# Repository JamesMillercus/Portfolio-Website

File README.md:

# Portfolio-Website
A repository containing the code for my portfolio website.

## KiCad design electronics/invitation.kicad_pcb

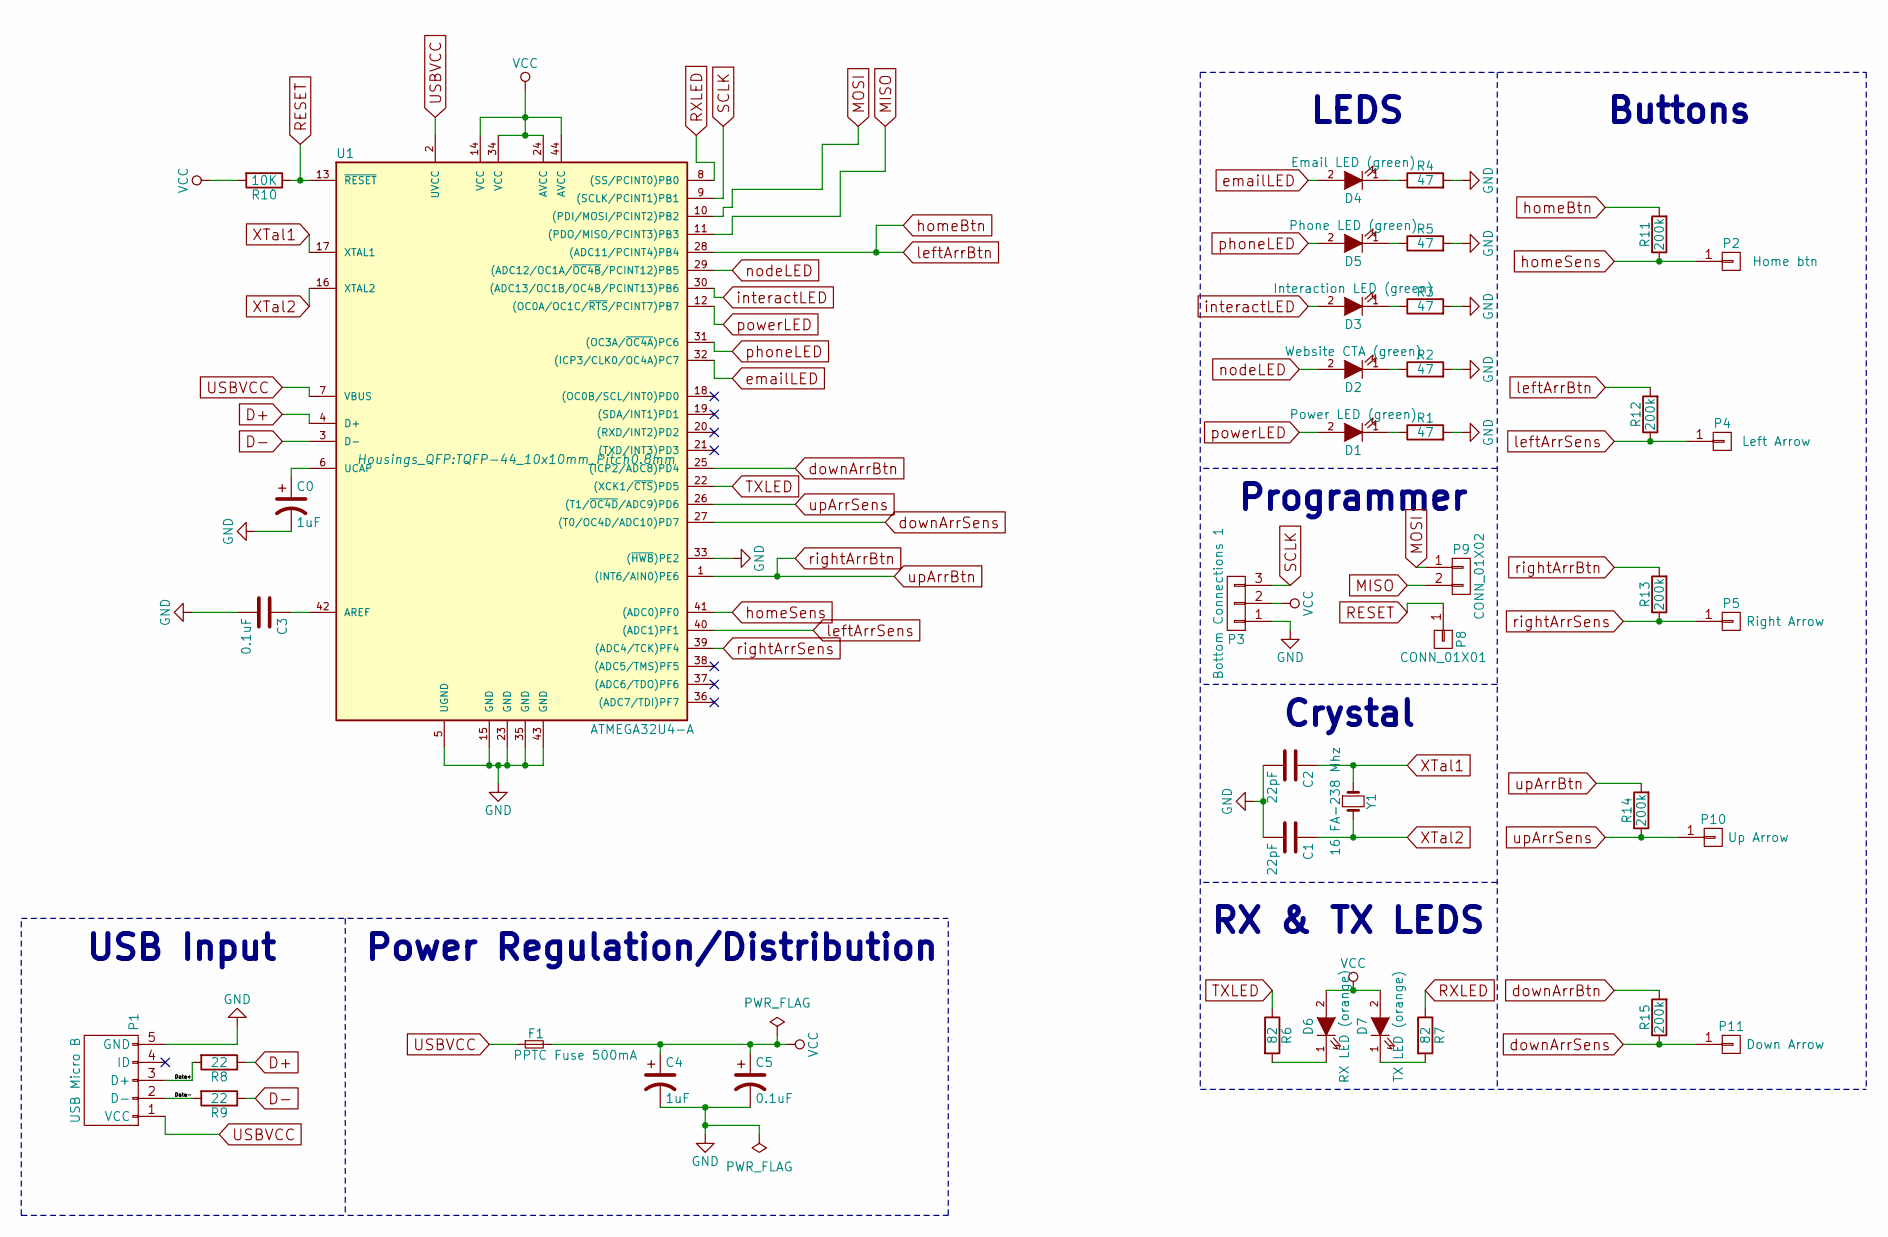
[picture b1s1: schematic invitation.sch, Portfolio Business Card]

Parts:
C0, C4: 1uF; CP_Tantalum_Case-R_EIA-2012-12_Reflow
C1, C2: 22pF; C_0805
C3: 0.1uF; C_0805
C5: 0.1uF; CP_Tantalum_Case-R_EIA-2012-12_Reflow
D1: Power LED (green); LED_0805
D2: Website CTA (green); LED_0805
D3: Interaction LED (green); LED_0805
D4: Email LED (green); LED_0805
D5: Phone LED (green); LED_0805
D6: RX LED (orange); LED_0805
D7: TX LED (orange); LED_0805
F1: PPTC Fuse 500mA; Fuse_SMD1206_Reflow
P1: USB Micro B; FCI_10103594-0001LF
P2: Home btn; JMLogoFinalSS
P3: Bottom Connections 1; SL-103-X-XX_1x03
P4: Left Arrow; leftArrowSS
P5: Right Arrow; rightArrowSS
P8: CONN_01X01; SL-101-X-XX_1x01
P9: CONN_01X02; SL-102-X-XX_1x02
P10: Up Arrow; upArrowSS
P11: Down Arrow; downArrowSS
R1, R2, R3, R4, R5: 47; R_0805
R6, R7: 82; R_0805
R8, R9: 22; R_0805
R10: 10K; R_0805
R11, R12, R13, R14, R15: 200k; R_0805_2012Metric
U1: ATMEGA32U4-A; TQFP-44_10x10mm_Pitch0.8mm
Y1: 16 FA-238 Mhz; crystal_FA238-TSX3225

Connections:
/Data+: P1.3 (D+), R8.2
/Data-: P1.2 (D-), R9.2
D+: R8.1, U1.4 (D+)
D-: R9.1, U1.3 (D-)
GND: C0.2, C1.2, C2.2, C3.2, C4.2, C5.2, P1.5 (GND), P3.1, R1.2, R2.2, R3.2, R4.2, R5.2, U1.5 (UGND), U1.15 (GND), U1.23 (GND), U1.33 ((~HWB~)PE2), U1.35 (GND), U1.43 (GND)
MISO: P9.2, U1.11 ((PDO/MISO/PCINT3)PB3)
MOSI: P9.1, U1.10 ((PDI/MOSI/PCINT2)PB2)
unnamed: C0.1, U1.6 (UCAP)
unnamed: C3.1, U1.42 (AREF)
unnamed: D1.1 (K), R1.1
unnamed: D2.1 (K), R2.1
unnamed: D3.1 (K), R3.1
unnamed: D4.1 (K), R4.1
unnamed: D5.1 (K), R5.1
unnamed: D6.1 (K), R6.2
unnamed: D7.1 (K), R7.2
RESET: P8.1, R10.1, U1.13 (~RESET~)
RXLED: R7.1, U1.8 ((SS/PCINT0)PB0)
SCLK: P3.3, U1.9 ((SCLK/PCINT1)PB1)
TXLED: R6.1, U1.22 ((XCK1/~CTS~)PD5)
USBVCC: F1.1, P1.1 (VCC), U1.2 (UVCC), U1.7 (VBUS)
VCC: C4.1, C5.1, D6.2 (A), D7.2 (A), F1.2, P3.2, R10.2, U1.14 (VCC), U1.24 (AVCC), U1.34 (VCC), U1.44 (AVCC)
XTal1: C2.1, U1.17 (XTAL1), Y1.1
XTal2: C1.1, U1.16 (XTAL2), Y1.2
downArrBtn: R15.2, U1.25 ((ICP2/ADC8)PD4)
downArrSens: P11.1, R15.1, U1.27 ((T0/OC4D/ADC10)PD7)
emailLED: D4.2 (A), U1.32 ((ICP3/CLK0/OC4A)PC7)
homeBtn: R11.2, R12.2, U1.28 ((ADC11/PCINT4)PB4)
homeSens: P2.1, R11.1, U1.41 ((ADC0)PF0)
interactLED: D3.2 (A), U1.30 ((ADC13/OC1B/OC4B/PCINT13)PB6)
leftArrSens: P4.1, R12.1, U1.40 ((ADC1)PF1)
nodeLED: D2.2 (A), U1.29 ((ADC12/OC1A/~OC4B~/PCINT12)PB5)
phoneLED: D5.2 (A), U1.31 ((OC3A/~OC4A~)PC6)
powerLED: D1.2 (A), U1.12 ((OC0A/OC1C/~RTS~/PCINT7)PB7)
rightArrBtn: R13.2, R14.2, U1.1 ((INT6/AIN0)PE6)
rightArrSens: P5.1, R13.1, U1.39 ((ADC4/TCK)PF4)
upArrSens: P10.1, R14.1, U1.26 ((T1/~OC4D~/ADC9)PD6)

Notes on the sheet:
USB Input
Power Regulation/Distribution
LEDS
Buttons
Programmer
RX & TX LEDS
Crystal

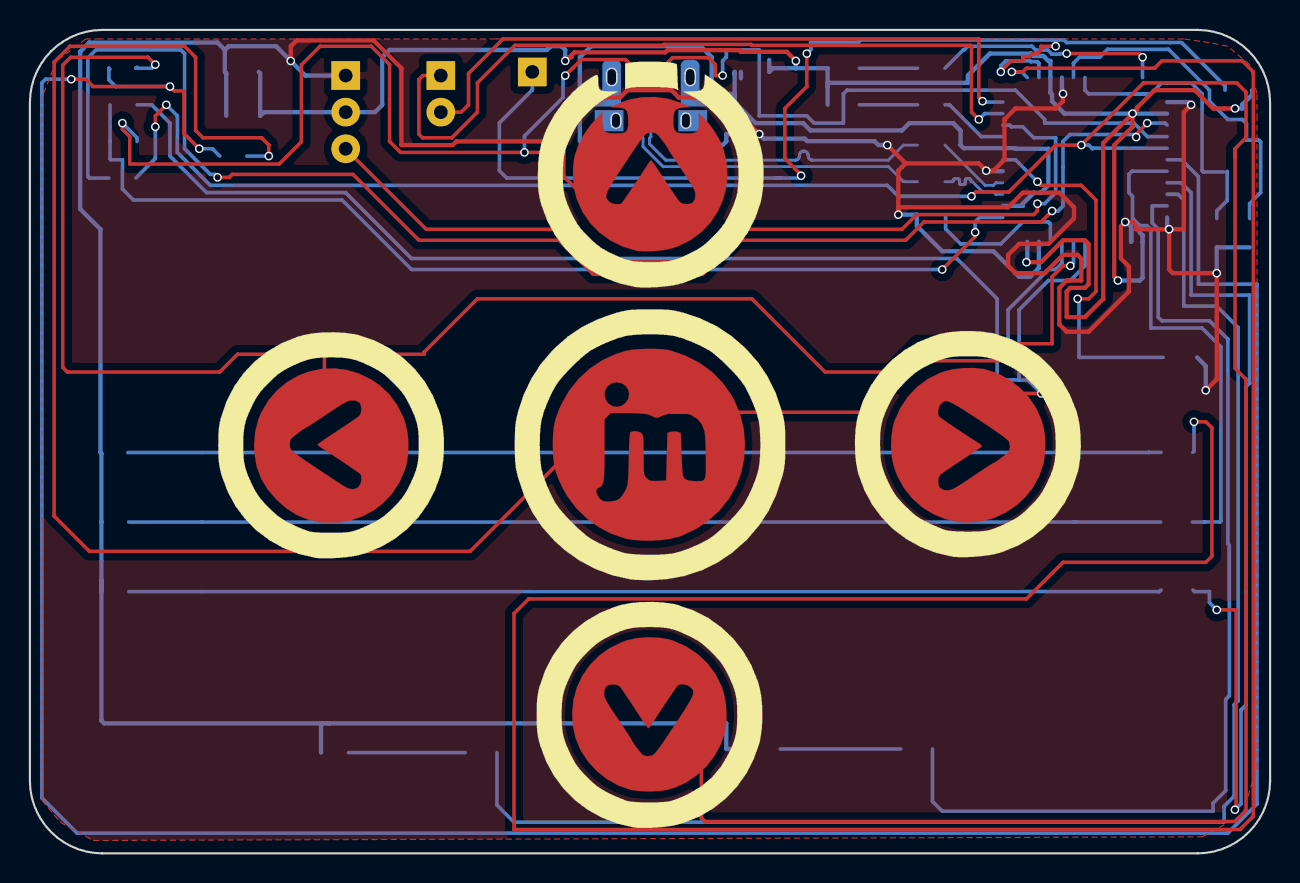
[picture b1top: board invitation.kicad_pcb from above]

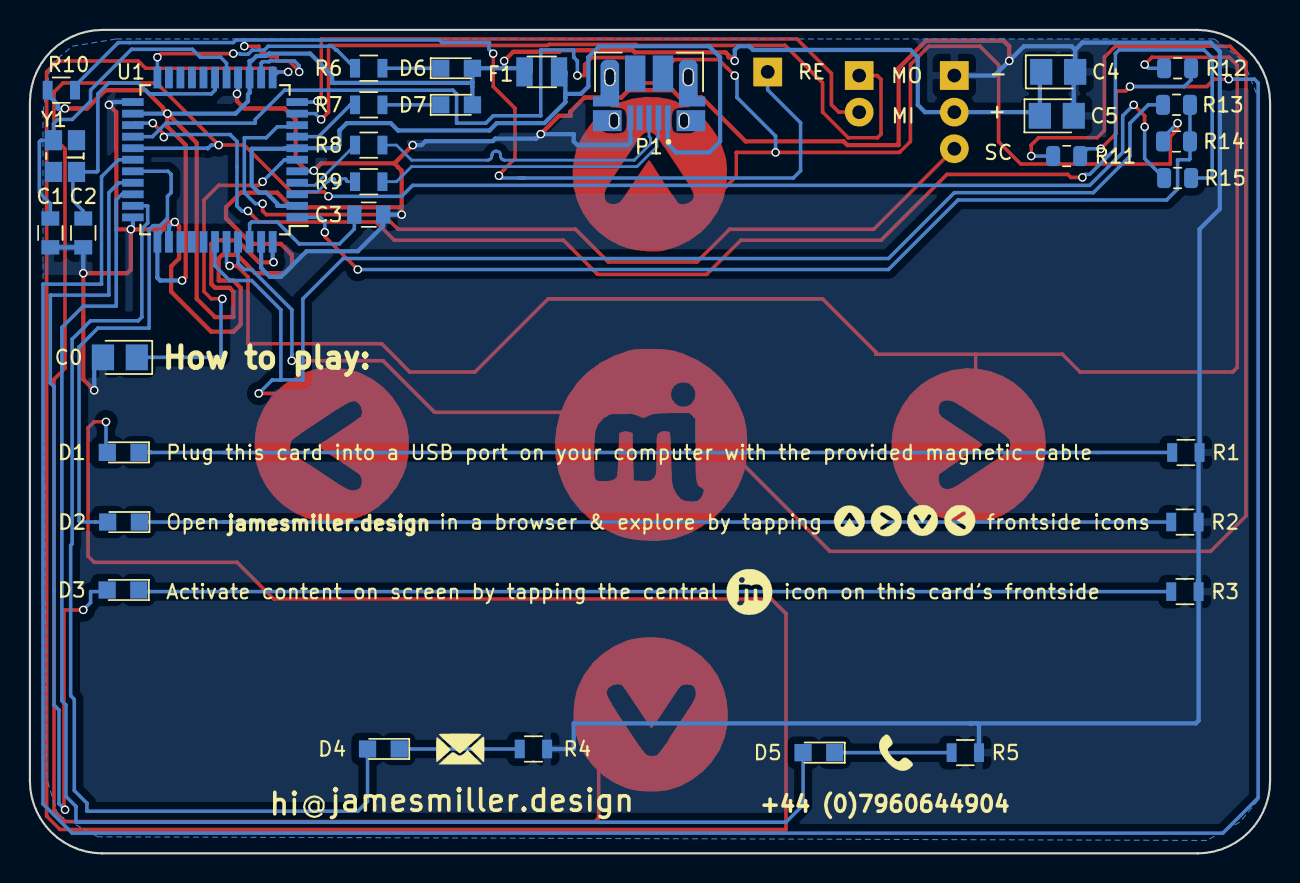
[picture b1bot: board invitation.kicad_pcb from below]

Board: 2 copper layers, 86.1 x 57.2 mm, 40 parts (32 on the bottom side), 37 nets.

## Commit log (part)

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2016-10-17 First commit: Uploading files to git for the first time.
2016-10-19 Commit 5: notes to myself about how to load videos
2016-10-24 Commit 7.1 - Updated Distribution folder with changes made in commit 7
2016-10-30 Commit 10:
    - When scrolled over, made videos auto play + reveal once they are loaded
2016-11-08 Commit 14:
    - Implemented full screen functionality
    - Still needs to be muted/unmuted + requires css changes on the video
2016-11-24 Commit 17 (whilst in LA): Added iPad + iPhone full screen video playing functionality
2016-12-02 Commit 21 (last commit before return to the UK): Fixed bugs with video opener and electronic invitation buttons, also implemented some design changes and prepared design assets for the plane journey
2016-12-06 Commit 25: Updated list of bugs to fix
2016-12-22 Commit 29: Fix scrolling bugs when initially loading the website and dragging mouse into browser, finalised central text functionality, added beer pump project.
2016-12-30 Commit 33: Updated hero changing function so that it only triggers if an Arduino is present, all logic is dealt with in the back end if hero does need to change (also means that if CMS is introduced,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
2017-01-16 Commit 38: Business card pre-production
2017-01-25 Commit 41: Updated Business Card BOM + PCB + Schematic to make sure components can be sourced.
2017-01-30 Commit 45: Continuing to optimise code by reprogramming global variables as objects.
2017-02-06 Commt 49: uncompleted changes
2017-02-18 Commit 53: Constructor function is now fully implemented
2017-09-11 Continue development on this branch.
2017-10-01 remove ignore
2017-10-02 SSL attempt
2017-10-28 PCB ready to print
2018-05-29 Implemented basic front end layout
2018-06-14 Scrolling animation positions and page sizing updated in preparation for item text content to be inserted
2018-07-02 Implemented device detection, browser detection needs state syncing
2018-07-06 Tidied Device and Browser detection HOCs
2018-07-08 Serving html content to screen, requires styling
2018-07-13 Prepared code ready for device specific functionality & styling
2018-07-17 Tidied Item component into ItemContainer and ItemText.
    To do:
    - Turn each component into a Tablet version, starting with GridContainer
2018-07-20 Implemented basic tablet functionality and made styling for device types even simpler by referencing .grid-container-${device} in scss
2018-07-22 Mail icon doesn’t open new tab
2018-07-26 Updated Merck and SAP golf gifs.
    Next step:
    - print out designs from pinterest into sketchbook
    - plan how the final designs will look
2018-08-04 Adjusting items to fit the new screen size
    Next steps:
    1. finish re-adjusting items to fit new screen size & make text look neater
    2. set heroLogo to expand to james miller on scroll over
    3. when scrolled out return to logo
    4. set hero text to normal font when icon scroll occurs
    5. set james miller to animate when scrolled over
2018-08-06 Prepared HeroText component for animation by tidying into parent and children
    Next steps:
    1. finalise design for logo and hero text
    2. hero text animation on change
    3. opening site animation
    4. implement for tablet & mobile
    5. design and implement error pages
2018-08-13 Finished implementing mouse scroll
    Next steps:
    1. hero text animation on change
    2. finalise colours for logo and hero text
    3. opening site animation
    4. implement for tablet & mobile
    5. design and implement error pages
2018-08-19 Continued to further reformat the hero text animation, steps to completion in code
    Next steps:
    1. hero text animation on change
    2. finalise colours for logo and hero text
    3. opening site animation
    4. Finalise hero area (text content, font, vertical / horizontal size of area)
    5. Animate hero to grow when scrolled over, items shrink
2018-08-26 hero nav updates almost complete
    Next steps:
    1. finalise colours for logo and hero text
    2. Finalise hero area (text content, font, vertical / horizontal size of area)
    3. Animate hero to grow when scrolled over, items shrink
    4. opening site animation
    Post alpha:
2018-08-30 Animated items
    Final alpha step:
    1. animate logo
    Beta:
    1. Design and implement error pages
    2. Final implementation for tablet & mobile
    3. Browser testing
2018-09-07 Mobile version complete
    Beta:
    1. Final implementation for tablet
    2. Browser testing
    3. Launch
    4. CodeSplitting
    5. Populate all social platforms with content
2018-09-12 Only enabled mouse movement on Chrome browser.
    To do: Windows 10: Fix hero area grid, Linux: test on camerons’s computer
    Beta:
    1. Final browser & device testing (launch)
    2. Prepare pages to be reusable (portfolio + tech pages)
    3. CodeSplitting
    4. Populate all social platforms with content
2018-09-16 SSL update
2018-09-21 Pages are prepared for reuse, tech page now created, animations implemented
    Beta:
    1. CodeSplitting (also get urls working in react)
    2. Populate all website + social platforms with content
    3. GDPR / Icons purchase (noun project) / copy right
2018-09-26 To do: Update heroIcons sizes for tech page, ready to put content in!!
    Beta:
    1. Populate all website + social platforms with content
    2. GDPR / Icons purchase (noun project) / copy right
    3. Jenkins (CI / CD)
2018-09-29 Updated GitHub and following links: apps, cms, architecture and blockchain links.
    Beta final to do:
    1. Content on other platforms (GitHub / LinkedIn / Behance / Hackster)
    2. Update visualise, prototype and IOT links
    3. Icons purchase (noun project) / copy right
2018-09-30 Beat Launched with CI!!!!!!!
2018-09-30 final push
2018-10-01 remove test
2018-10-01 push analytics
2018-10-04 push linkedin profile
2018-10-07 Update .rancher-pipeline.yml file
2018-10-07 test 3
2018-10-07 test 7
2018-10-07 launch site
2018-10-15 Hero Area styled
    - Implement config file for hero area
    - Implement redux
    - Break down Hero Area into multiple nested components
    - item component
    - video component
    - rework website for react360
2018-10-18 set variables from config via home page, tidy file structure (putting components into folders)
    to do:
    - ideally render content without renderToSurface
    - Either remove redux and routing, implement fake redux and all logic goes in client.js (not ideal)
    - implement functionality to render 3d objects within components
    - create services page
    - item component
2018-10-22 integrated scroll and click redux into the item component
    to do:
    - finish item component
    - video component
    - animation
    - create services page
    - integrate into reactjs app
2018-10-24 Working on video component, implemented native modules to resize 360 surfaces (woohoo)
    to do:
    - implement global redux-like store
    - video component
    - animation
    - create services page
    - integrate into reactjs app
2018-10-29 - completed video component playback
    to do:
    - redo app architecture to allow creation of all 8 items
    - test on mobile, tablet, oculus and vive
    - implement no script (error page)
    - implement error page for faulty/no accelerometer
2018-11-06 Implemented no script (error page)
    to do:
    - implement webvr button for mobile
    - implement error page for faulty/no accelerometer
    - test on mobile, tablet, oculus and vive
2018-11-09 Updated Webvr video component
2018-11-19 updated copy
2018-11-26 Implementing keyboard functionality, next step is to complete menu scrolling.
2018-12-12 Implementing keyboard functionality
    To do:
    - Complete electronic invite keyboard functionality (open hero feature)
    - Implement webvr-polyfill for mobile
    - More intuitive UX for webvr laptop experience
    - Fix getOSVersion.js HOC (in Lincoln)
    - Auto go-to webvr page on mobile if on iOS or android version .4 or higher
2018-12-19 Implemented functionality to switch between react360 / react versions of site based on device os.
    - Implement 2 versions of react360
    1. Webvr-polyfill for mobile (using Compositor.js), design & dev for gaze functionality
    2. Webvr laptop & mobile experience (Appropriate UX / UI for both)
    - Fix getOSVersion.js HOC (in Lincoln)
2019-01-02 Implemented gaze functionality for Hero, next stop is the Items (create circle hitbox around itemImage)
    - Complete react360
    1. Implement gaze functionality for polyfill version + design instruction page (implement in normal react).
    2. Instruction page for laptop + mobile version (implement in normal react).
    3. Enable click functionality for mobile non-webvr (without pointer)
    4. Fix video bugs and allow webvr version to play video without youtube (like laptop version)
    - Fix getOSVersion.js HOC (in Lincoln)
2019-01-10 Fixed bug for exiting videos on mobile + mobile webvr
    - Complete in react
    1. Design instruction page for mobile webvr + mobile + laptop
    2. Fix getOSVersion.js HOC (in Lincoln)
    - Rethink UX for site that gets you to pages
2019-01-21 Finished layout for instruction page.
    - Complete in react
    1. Detect if using VR headset
    - display different instructions for webvr
    - don’t allow split screen
    - don’t display non-webvr web page
    2. Create content for instruction page on headset webvr + mobile webvr + mobile + laptop
2019-02-17 Updated electronics for Chinese suppliers (V10) and allowed device type detection for react360 device based experiences.
    - To complete
    1. Display appropriate VR content based on device
    - vertical mobile display message to turn phone horizontally
    - iOS chrome iframe not playing when clicked!
    - VR instructions and video not working
    2. Create content for instruction page on headset webvr + mobile webvr + mobile + laptop
2019-05-13 Mobile (normal and WebVR) content and mobile interaction complete
    - To do
    1. Create content for
    a) instruction page
    laptop ( webvr / nonwebvr)
    b) updated projects (Egypt based on app content)
2019-05-22 Updated egypt css
    - To do
    a) update PCB (resize email icon to be bigger) and then purchase after latest test
    b) create final prototype box with a test letter
    c) order and assemble multiples
2019-06-13 Updated exit button on mobile
    - To do
    a) update PCB (resize email icon to be bigger) and then purchase after latest test
    b) order and assemble multiples
    c) update website’s small bugs & UX issues
    1) prevent page from zooming in on mobile webvr screen
    2) fix on (digital design’s) large screen
2019-12-03 Updated assets and AWS integration
2019-12-05 buildspec integration
2019-12-05 docker trial
2019-12-05 update to docker
2020-09-05 Bump handlebars from 4.0.12 to 4.7.6 in /web/react360
    Bumps [handlebars](https://github.com/wycats/handlebars.js) from 4.0.12 to 4.7.6.
    - [Release notes](https://github.com/wycats/handlebars.js/releases)
    - [Changelog](https://github.com/handlebars-lang/handlebars.js/blob/master/release-notes.md)
    - [Commits](https://github.com/wycats/handlebars.js/compare/v4.0.12...v4.7.6)
2020-09-29 Bump merge from 1.2.0 to 1.2.1 in /web/react360
    Bumps [merge](https://github.com/yeikos/js.merge) from 1.2.0 to 1.2.1.
    - [Release notes](https://github.com/yeikos/js.merge/releases)
    - [Commits](https://github.com/yeikos/js.merge/compare/v1.2.0...v1.2.1)
